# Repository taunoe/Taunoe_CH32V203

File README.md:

# My CH32V203 Development Boards

Here I will start to develop my CH32V203 development boards and collect all related materials.

## Code

[Example code](./Example_code/README.md)

## WCH Docs

- [CH32V203 Datasheet](doc/CH32V203DS0.PDF)
- [CH32F/V20x_V30x_V31x Reference Manual](doc/CH32FV2x_V3xRM.PDF)
- [CH32V20x Evaluation Board Reference](doc/CH32V20x_Evaluation_Board_Reference-EN.pdf)
- [CH32V20x Schematics](doc/CH32V20xSCH.pdf)
- [QingKeV4 Microprocessor Manual](doc/QingKeV4_Processor_Manual.PDF)
- [WCH Touch Application Guide](doc/WCH_TouchApplicationGuide.PDF)
- [Common Package Dimensions for CH Series ICs](doc/PACKAGE.PDF)

## CH32V203F6P6

Chip ID: 20370510

Chip size:

Pinout:

My board schematics

My board pinout:

### UART

* TX -> PA3
* RX -> PA2

## CH32V203C8T6

ChipID: 20310500

Chip size:

## UART

* TX -> PA10 = A10 (WeActStudio Blue Pill Plus)
* RX -> PA9  = A9 (WeActStudio Blue Pill Plus)

_______________
Tauno Erik ♥ Väimela ♥ 2025

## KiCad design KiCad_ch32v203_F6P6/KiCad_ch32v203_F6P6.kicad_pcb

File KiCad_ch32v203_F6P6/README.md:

# CH32V203F6P6

This design uses components with a size 1206.

_______________
Tauno Erik ♥ Väimela ♥ 2025

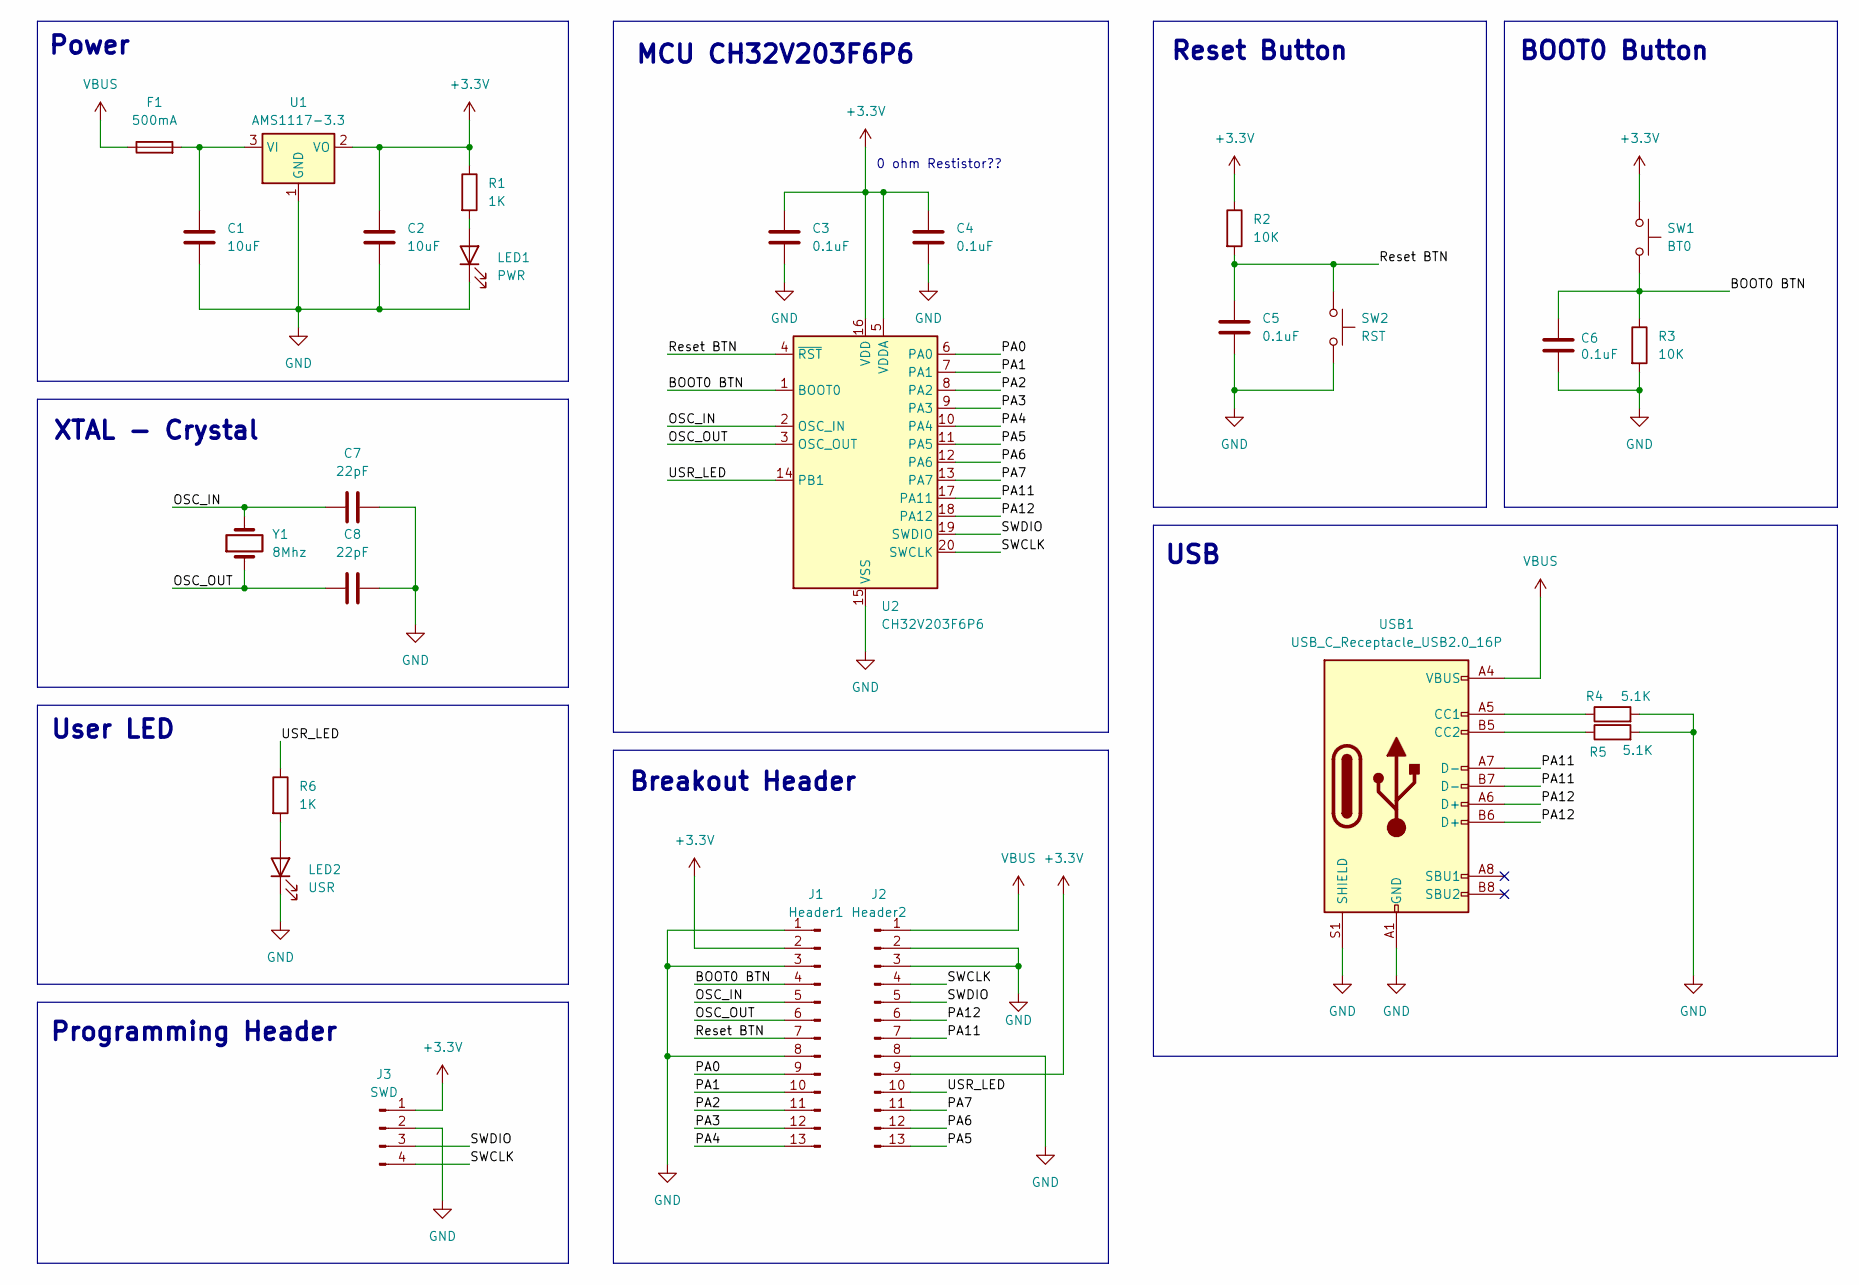
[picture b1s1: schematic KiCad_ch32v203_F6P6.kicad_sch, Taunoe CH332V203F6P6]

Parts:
C1, C2: 10uF; C_1206_3216Metric_Pad1.33x1.80mm_HandSolder
C3, C4, C5, C6: 0.1uF; C_1206_3216Metric_Pad1.33x1.80mm_HandSolder
C7, C8: 22pF; C_1206_3216Metric_Pad1.33x1.80mm_HandSolder
F1: 500mA; Fuse_1206_3216Metric_Pad1.42x1.75mm_HandSolder
J1: Header1; PinHeader_1x13_P2.54mm_Vertical
J2: Header2; PinHeader_1x13_P2.54mm_Vertical
J3: SWD; PinHeader_1x04_P2.54mm_Vertical
LED1: PWR; LED_1206_3216Metric_Pad1.42x1.75mm_HandSolder
LED2: USR; LED_1206_3216Metric_Pad1.42x1.75mm_HandSolder
R1, R6: 1K; R_1206_3216Metric_Pad1.30x1.75mm_HandSolder
R2, R3: 10K; R_1206_3216Metric_Pad1.30x1.75mm_HandSolder
R4, R5: 5.1K; R_1206_3216Metric_Pad1.30x1.75mm_HandSolder
SW1: BT0; Push_button_smd_3x4x2_2pin
SW2: RST; Push_button_smd_3x4x2_2pin
U1: AMS1117-3.3; SOT-223-3_TabPin2
U2: CH32V203F6P6; TSSOP-20_4.4x6.5mm_P0.65mm
USB1: USB_C_Receptacle_USB2.0_16P; USB_C_Receptacle_HCTL_HC-TYPE-C-16P-01A
Y1: 8Mhz; Crystal_SMD_5032-2Pin_5.0x3.2mm

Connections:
+3.3V: C2.1, C3.1, C4.1, J1.2, J2.9, J3.1, R1.1, R2.1, SW1.1, U1.2 (VO), U2.5 (VDDA), U2.16 (VDD)
/BOOT0 BTN: C6.1, J1.4, R3.1, SW1.2, U2.1 (BOOT0)
/OSC_IN: C7.1, J1.5, U2.2 (OSC_IN), Y1.2
/OSC_OUT: C8.1, J1.6, U2.3 (OSC_OUT), Y1.1
/PA0: J1.9, U2.6 (PA0)
/PA1: J1.10, U2.7 (PA1)
/PA2: J1.11, U2.8 (PA2)
/PA3: J1.12, U2.9 (PA3)
/PA4: J1.13, U2.10 (PA4)
/PA5: J2.13, U2.11 (PA5)
/PA6: J2.12, U2.12 (PA6)
/PA7: J2.11, U2.13 (PA7)
/PA11: J2.7, U2.17 (PA11), USB1.A7 (D-), USB1.B7 (D-)
/PA12: J2.6, U2.18 (PA12), USB1.A6 (D+), USB1.B6 (D+)
/Reset BTN: C5.1, J1.7, R2.2, SW2.1, U2.4 (~RST)
/SWCLK: J2.4, J3.4, U2.20 (SWCLK)
/SWDIO: J2.5, J3.3, U2.19 (SWDIO)
/USR_LED: J2.10, R6.1, U2.14 (PB1)
GND: C1.2, C2.2, C3.2, C4.2, C5.2, C6.2, C7.2, C8.2, J1.1, J1.3, J1.8, J2.2, J2.3, J2.8, J3.2, LED1.1 (K), LED2.1 (K), R3.2, R4.2, R5.2, SW2.2, U1.1 (GND), U2.15 (VSS), USB1.A1 (GND), USB1.A12 (GND), USB1.B1 (GND), USB1.B12 (GND), USB1.S1 (SHIELD)
unnamed: LED1.2 (A), R1.2
unnamed: LED2.2 (A), R6.2
unnamed: C1.1, F1.2, U1.3 (VI)
unnamed: R4.1, USB1.A5 (CC1)
unnamed: R5.1, USB1.B5 (CC2)
VBUS: F1.1, J2.1, USB1.A4 (VBUS), USB1.A9 (VBUS), USB1.B4 (VBUS), USB1.B9 (VBUS)

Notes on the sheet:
Power
MCU CH32V203F6P6
0 ohm Restistor??
USB
XTAL - Crystal
BOOT0 Button
Breakout Header
User LED
Programming Header
Reset Button

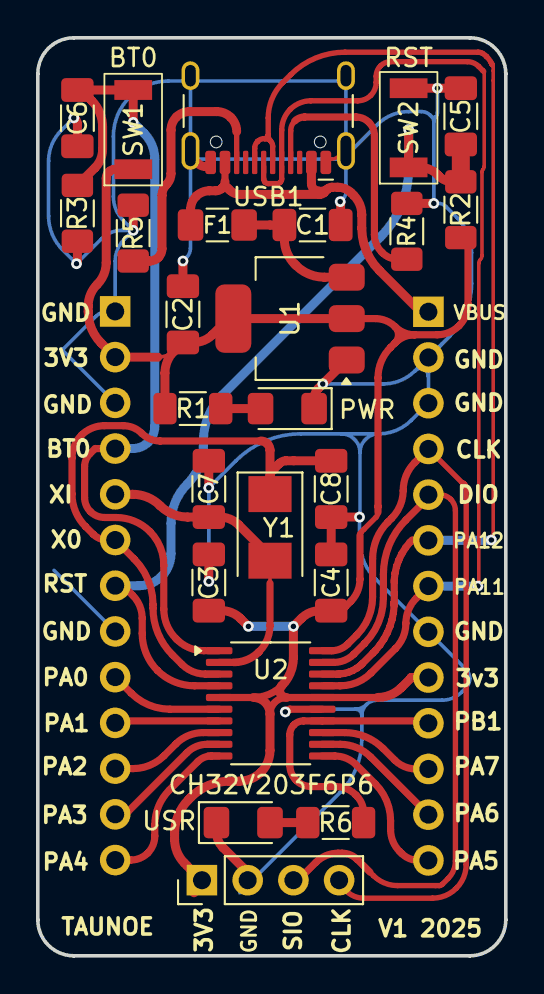
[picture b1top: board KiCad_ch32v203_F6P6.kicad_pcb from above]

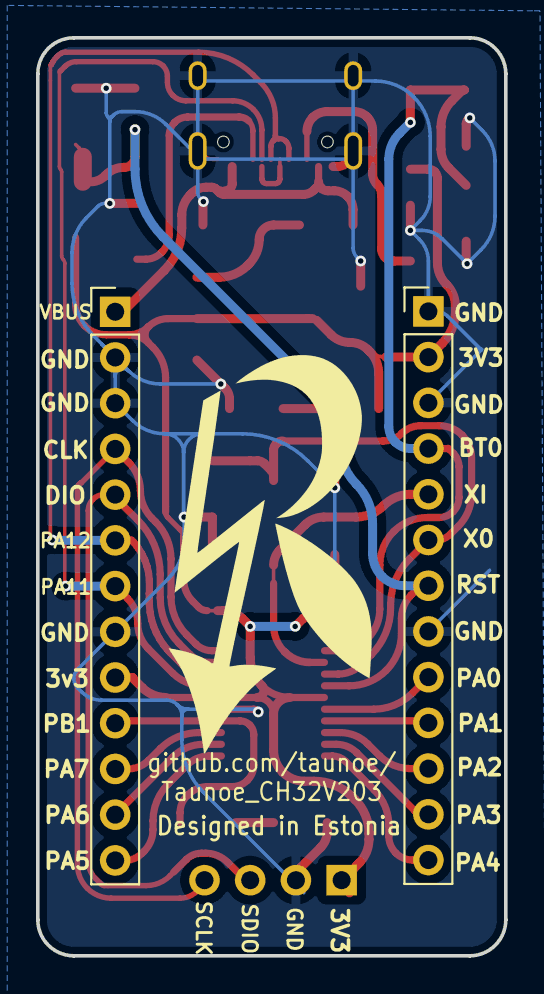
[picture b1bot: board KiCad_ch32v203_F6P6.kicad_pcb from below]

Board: 2 copper layers, 26.0 x 51.0 mm, 26 parts (2 on the bottom side), 25 nets.

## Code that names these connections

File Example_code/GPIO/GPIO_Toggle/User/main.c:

/********************************** (C) COPYRIGHT *******************************
 * File Name          : main.c
 * Author             : Tauno Erik
 * Version            : V1.0.0
 * Date               : 2025-05-21
 * Description        : GPIO pins

 *******************************************************************************/

#include "debug.h"
#include <stdio.h>
#include <inttypes.h> // For PRIu32

/* Global define */
#define DELAY_VAL 250

/* Global Variable */

/*********************************************************************
 * @fn      GPIO_Toggle_INIT
 *
 * @brief   Initializes GPIOA.0
 *
 * @return  none
 */
void init_PA0(void)
{
    GPIO_InitTypeDef GPIO_InitStructure = {0};

    RCC_APB2PeriphClockCmd(RCC_APB2Periph_GPIOA, ENABLE); // GPIOA

    GPIO_InitStructure.GPIO_Pin = GPIO_Pin_0;
    GPIO_InitStructure.GPIO_Mode = GPIO_Mode_Out_PP; // Push-Pull
    GPIO_InitStructure.GPIO_Speed = GPIO_Speed_50MHz;
    GPIO_Init(GPIOA, &GPIO_InitStructure);
}

void init_PA1(void)
{
    // 1. Define the GPIO Initialization Structure
    GPIO_InitTypeDef GPIO_InitStructure = {0};

    // 2. Enable the APB2 Clock for GPIOA
    // GPIOA is connected to the APB2 bus.
    RCC_APB2PeriphClockCmd(RCC_APB2Periph_GPIOA, ENABLE);

    // 3. Configure Pin PA1
    GPIO_InitStructure.GPIO_Pin = GPIO_Pin_1;         // Select Pin 1
    GPIO_InitStructure.GPIO_Mode = GPIO_Mode_Out_PP;  // Set as Output Push-Pull
    GPIO_InitStructure.GPIO_Speed = GPIO_Speed_50MHz; // Set the output speed

    // 4. Apply the configuration to GPIOA
    GPIO_Init(GPIOA, &GPIO_InitStructure);
}

void init_PA4(void)
{
    // 1. Define the GPIO Initialization Structure
    GPIO_InitTypeDef GPIO_InitStructure = {0};

    // 2. Enable the APB2 Clock for GPIOA
    // GPIOA is connected to the APB2 bus.
    RCC_APB2PeriphClockCmd(RCC_APB2Periph_GPIOA, ENABLE);

    // 3. Configure Pin PA1
    GPIO_InitStructure.GPIO_Pin = GPIO_Pin_4;         // Select Pin 1
    GPIO_InitStructure.GPIO_Mode = GPIO_Mode_Out_PP;  // Set as Output Push-Pull
    GPIO_InitStructure.GPIO_Speed = GPIO_Speed_50MHz; // Set the output speed

    // 4. Apply the configuration to GPIOA
    GPIO_Init(GPIOA, &GPIO_InitStructure);
}

void init_PA5(void)
{
    // 1. Define the GPIO Initialization Structure
    GPIO_InitTypeDef GPIO_InitStructure = {0};

    // 2. Enable the APB2 Clock for GPIOA
    // GPIOA is connected to the APB2 bus.
    RCC_APB2PeriphClockCmd(RCC_APB2Periph_GPIOA, ENABLE);

    // 3. Configure Pin PA1
    GPIO_InitStructure.GPIO_Pin = GPIO_Pin_5;         // Select Pin 1
    GPIO_InitStructure.GPIO_Mode = GPIO_Mode_Out_PP;  // Set as Output Push-Pull
    GPIO_InitStructure.GPIO_Speed = GPIO_Speed_50MHz; // Set the output speed

    // 4. Apply the configuration to GPIOA
    GPIO_Init(GPIOA, &GPIO_InitStructure);
}

void init_PA6(void)
{
    // 1. Define the GPIO Initialization Structure
    GPIO_InitTypeDef GPIO_InitStructure = {0};

    // 2. Enable the APB2 Clock for GPIOA
    // GPIOA is connected to the APB2 bus.
    RCC_APB2PeriphClockCmd(RCC_APB2Periph_GPIOA, ENABLE);

    // 3. Configure Pin PA1
    GPIO_InitStructure.GPIO_Pin = GPIO_Pin_6;         // Select Pin 1
    GPIO_InitStructure.GPIO_Mode = GPIO_Mode_Out_PP;  // Set as Output Push-Pull
    GPIO_InitStructure.GPIO_Speed = GPIO_Speed_50MHz; // Set the output speed

    // 4. Apply the configuration to GPIOA
    GPIO_Init(GPIOA, &GPIO_InitStructure);
}

void init_PA7(void)
{
    // 1. Define the GPIO Initialization Structure
    GPIO_InitTypeDef GPIO_InitStructure = {0};

    // 2. Enable the APB2 Clock for GPIOA
    // GPIOA is connected to the APB2 bus.
    RCC_APB2PeriphClockCmd(RCC_APB2Periph_GPIOA, ENABLE);

    // 3. Configure Pin PA1
    GPIO_InitStructure.GPIO_Pin = GPIO_Pin_7;         // Select Pin 1
    GPIO_InitStructure.GPIO_Mode = GPIO_Mode_Out_PP;  // Set as Output Push-Pull
    GPIO_InitStructure.GPIO_Speed = GPIO_Speed_50MHz; // Set the output speed

    // 4. Apply the configuration to GPIOA
    GPIO_Init(GPIOA, &GPIO_InitStructure);
}

void init_PB1(void) // On board LED
{
    // 1. Define the GPIO Initialization Structure
    GPIO_InitTypeDef GPIO_InitStructure = {0};

    // 2. Enable the APB2 Clock for GPIOA
    // GPIOA is connected to the APB2 bus.
    RCC_APB2PeriphClockCmd(RCC_APB2Periph_GPIOB, ENABLE);

    // 3. Configure Pin PA1
    GPIO_InitStructure.GPIO_Pin = GPIO_Pin_1;         // Select Pin 1
    GPIO_InitStructure.GPIO_Mode = GPIO_Mode_Out_PP;  // Set as Output Push-Pull
    GPIO_InitStructure.GPIO_Speed = GPIO_Speed_50MHz; // Set the output speed

    // 4. Apply the configuration to GPIOA
    GPIO_Init(GPIOB, &GPIO_InitStructure);
}

void init_PA11(void)
{
    // 1. Define the GPIO Initialization Structure
    GPIO_InitTypeDef GPIO_InitStructure = {0};

    // 2. Enable the APB2 Clock for GPIOA
    // GPIOA is connected to the APB2 bus.
    RCC_APB2PeriphClockCmd(RCC_APB2Periph_GPIOA, ENABLE);

    // 3. Configure Pin PA1
    GPIO_InitStructure.GPIO_Pin = GPIO_Pin_11;         // Select Pin 1
    GPIO_InitStructure.GPIO_Mode = GPIO_Mode_Out_PP;  // Set as Output Push-Pull
    GPIO_InitStructure.GPIO_Speed = GPIO_Speed_50MHz; // Set the output speed

    // 4. Apply the configuration to GPIOA
    GPIO_Init(GPIOA, &GPIO_InitStructure);
}

void init_PA12(void)
{
    // 1. Define the GPIO Initialization Structure
    GPIO_InitTypeDef GPIO_InitStructure = {0};

    // 2. Enable the APB2 Clock for GPIOA
    // GPIOA is connected to the APB2 bus.
    RCC_APB2PeriphClockCmd(RCC_APB2Periph_GPIOA, ENABLE);

    // 3. Configure Pin PA1
    GPIO_InitStructure.GPIO_Pin = GPIO_Pin_12;         // Select Pin 1
    GPIO_InitStructure.GPIO_Mode = GPIO_Mode_Out_PP;  // Set as Output Push-Pull
    GPIO_InitStructure.GPIO_Speed = GPIO_Speed_50MHz; // Set the output speed

    // 4. Apply the configuration to GPIOA
    GPIO_Init(GPIOA, &GPIO_InitStructure);
}

/*********************************************************************
 * @fn      main
 *
 * @brief   Main program.
 *
 * @return  none
 */
int main(void)
{
    uint32_t  i = 0;

    NVIC_PriorityGroupConfig(NVIC_PriorityGroup_1);
    SystemCoreClockUpdate();
    Delay_Init();
    USART_Printf_Init(115200);
    printf("SystemClk:%d\r\n", SystemCoreClock);
    printf( "ChipID:%08x\r\n", DBGMCU_GetCHIPID() );
    printf("GPIO Toggle TEST\r\n");
    init_PA0();
    init_PA1();
    init_PA4();
    init_PA5();
    init_PA6();
    init_PA7();
    init_PB1();
    init_PA11();
    init_PA12();

    while(1)
    {
        //GPIO_WriteBit(GPIOA, GPIO_Pin_0, (i == 0) ? (i = Bit_SET) : (i = Bit_RESET));
        i++;

        // PA0
        GPIO_WriteBit(GPIOA, GPIO_Pin_0, Bit_SET);   // Set PA0 High
        Delay_Ms(DELAY_VAL);
        GPIO_WriteBit(GPIOA, GPIO_Pin_0, Bit_RESET); // Set PA0 Low
        Delay_Ms(DELAY_VAL);

        // PA1
        GPIO_WriteBit(GPIOA, GPIO_Pin_1, Bit_SET);   // Set PA1 High
        Delay_Ms(DELAY_VAL);
        GPIO_WriteBit(GPIOA, GPIO_Pin_1, Bit_RESET); // Set PA1 Low
        Delay_Ms(DELAY_VAL);

        //PA4
        GPIO_WriteBit(GPIOA, GPIO_Pin_4, Bit_SET);   // Set PA4 High
        Delay_Ms(DELAY_VAL);
        GPIO_WriteBit(GPIOA, GPIO_Pin_4, Bit_RESET); // Set PA4 Low
        Delay_Ms(DELAY_VAL);

        //PA5
        GPIO_WriteBit(GPIOA, GPIO_Pin_5, Bit_SET);   // Set PA5 High
        Delay_Ms(DELAY_VAL);
        GPIO_WriteBit(GPIOA, GPIO_Pin_5, Bit_RESET); // Set PA5 Low
        Delay_Ms(DELAY_VAL);

        //PA6
        GPIO_WriteBit(GPIOA, GPIO_Pin_6, Bit_SET);   // Set PA6 High
        Delay_Ms(DELAY_VAL);
        GPIO_WriteBit(GPIOA, GPIO_Pin_6, Bit_RESET); // Set PA6 Low
        Delay_Ms(DELAY_VAL);

        //PA7
        GPIO_WriteBit(GPIOA, GPIO_Pin_7, Bit_SET);   // Set PA7 High
        Delay_Ms(DELAY_VAL);
        GPIO_WriteBit(GPIOA, GPIO_Pin_7, Bit_RESET); // Set PA7 Low
        Delay_Ms(DELAY_VAL);

        // PB1
        GPIO_WriteBit(GPIOB, GPIO_Pin_1, Bit_SET);   // Set PB1 High
        Delay_Ms(DELAY_VAL);
        GPIO_WriteBit(GPIOB, GPIO_Pin_1, Bit_RESET); // Set PB1 Low
        Delay_Ms(DELAY_VAL);

        // PA11
        GPIO_WriteBit(GPIOA, GPIO_Pin_11, Bit_SET);   // Set PA11 High
        Delay_Ms(DELAY_VAL);
        GPIO_WriteBit(GPIOA, GPIO_Pin_11, Bit_RESET); // Set PA11 Low
        Delay_Ms(DELAY_VAL);

        // PA12
        GPIO_WriteBit(GPIOA, GPIO_Pin_12, Bit_SET);   // Set PA12 High
        Delay_Ms(DELAY_VAL);
        GPIO_WriteBit(GPIOA, GPIO_Pin_12, Bit_RESET); // Set PA12 Low
        Delay_Ms(DELAY_VAL);

        printf("i = %" PRIu32 "\r\n", i);
    }
}

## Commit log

2025-03-21 code index
2025-03-22 index
2025-03-25 first schematics
2025-03-26 started board file
2025-03-27 Rell!
2025-03-28 kicad silkscreen
2025-03-29 board ready
2025-04-26 pinout
2025-05-24 gpio code
2025-05-25 sysTick interrupt
2025-05-25 systic
2025-05-31 keyboard test
